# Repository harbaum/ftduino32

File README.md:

# ftDuino32

The ftDuino32 is the big brother of the [ftDuino](http://ftDuino.de). Read [more about the ftDuino32](https://harbaum.github.io/ftduino32/www/).

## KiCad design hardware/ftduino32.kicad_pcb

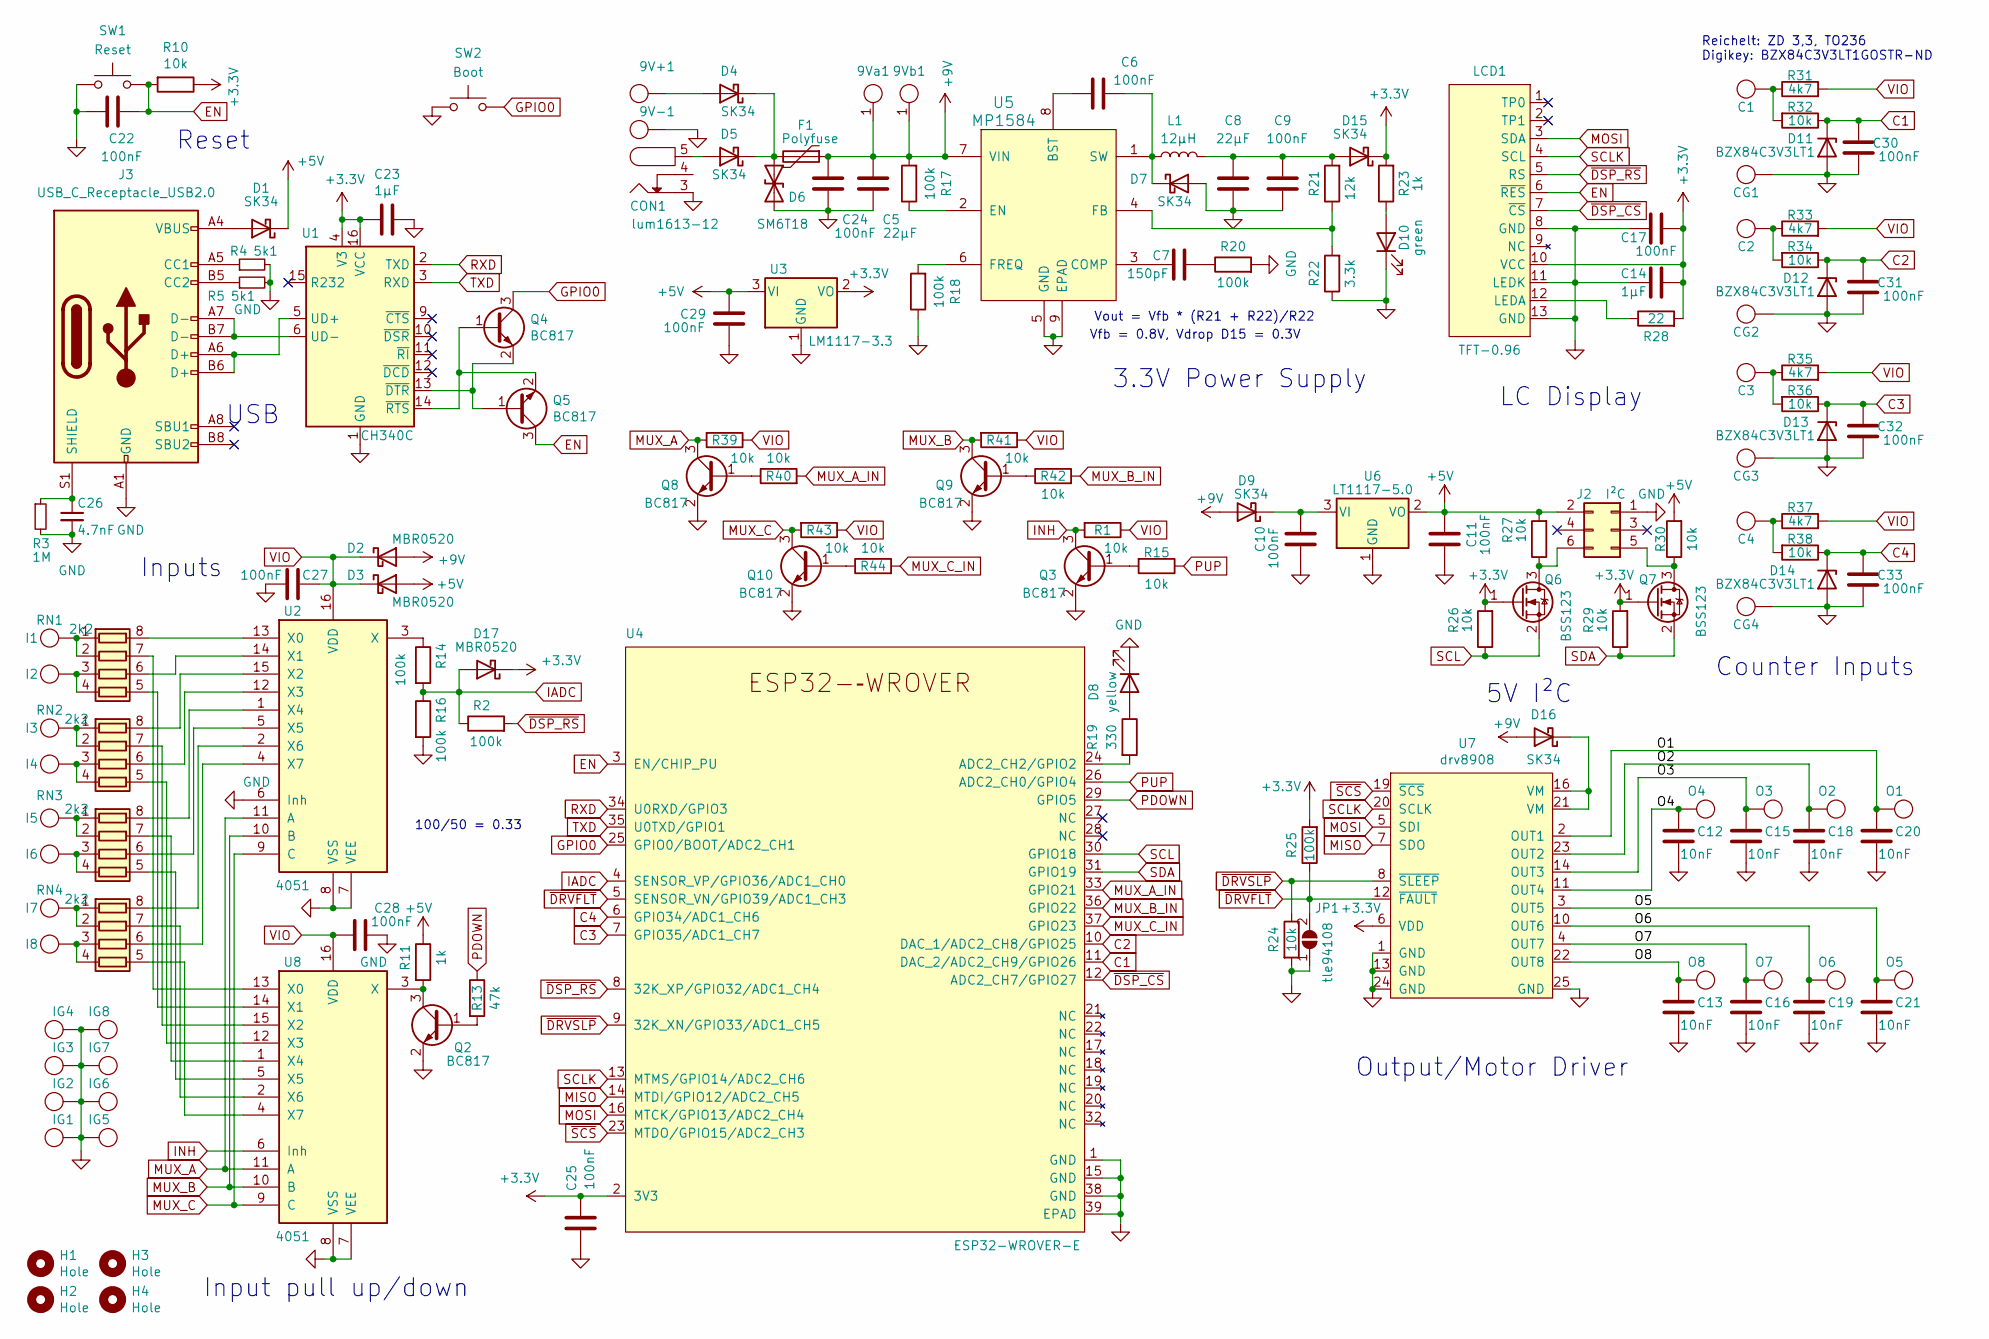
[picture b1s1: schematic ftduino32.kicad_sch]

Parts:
9V+1, 9V-1, 9Va1, 9Vb1: Sleeve; sleeve
C1, C2, C3, C4: Sleeve; sleeve
C5, C8: 22µF; C_1206_3216Metric; LCSC C12891
C6, C9, C10, C11, C17, C22, C24, C25, C27, C28, C29, C30, C31, C32, C33: 100nF; C_0805_2012Metric
C7: 150pF; C_0805_2012Metric
C12, C13, C15, C16, C18, C19, C20, C21: 10nF; C_0805_2012Metric
C14, C23: 1µF; C_0805_2012Metric
C26: 4.7nF; C_0805_2012Metric
CG1, CG2, CG3, CG4: Sleeve; sleeve
CON1: lum1613-12
D1, D4, D5, D7, D9, D15, D16: SK34; D_SMA; LCSC C8678
D2, D3, D17: MBR0520; D_SOD-123
D6: SM6T18; D_SMB
D8: yellow; LED_0805_2012Metric; LCSC C2296
D10: green; LED_0805_2012Metric; LCSC C2297
D11, D12, D13, D14: BZX84C3V3LT1; D_SOT-23_ANK; JLCPCB Rotation Offset 180
F1: Polyfuse; Fuse_1812_4532Metric; LCSC C207074
H1, H2, H3, H4: Hole; MountingHole_3mm
I1, I2, I3, I4, I5, I6, I7, I8: Sleeve; sleeve
IG1, IG2, IG3, IG4, IG5, IG6, IG7, IG8: Sleeve; sleeve
J2: I²C; PinHeader_2x03_P2.54mm_Vertical
J3: USB_C_Receptacle_USB2.0; TYPE-C-31-M-12; LCSC Part # C2927037
JP1: tle94108; SolderJumper-2_P1.3mm_Open_RoundedPad1.0x1.5mm
L1: 12µH; L_Abracon_ASPI-0630LR; LCSC C380177
LCD1: TFT-0.96
O1, O2, O3, O4, O5, O6, O7, O8: Sleeve; sleeve
Q2, Q3, Q4, Q5, Q8, Q9, Q10: BC817; SOT-23; JLCPCB Rotation Offset 180
Q6, Q7: BSS123; SOT-23; JLCPCB Rotation Offset 180
R1, R10, R15, R24, R26, R27, R29, R30, R32, R34, R36, R38, R39, R40, R41, R42, R43, R44: 10k; R_0805_2012Metric
R2, R14, R16, R17, R18, R20, R25: 100k; R_0805_2012Metric
R3: 1M; R_0805_2012Metric
R4, R5: 5k1; R_0805_2012Metric
R11, R23: 1k; R_0805_2012Metric
R13: 47k; R_0805_2012Metric
R19: 330; R_0805_2012Metric
R21: 12k; R_0805_2012Metric
R22: 3.3k; R_0805_2012Metric
R28: 22; R_0805_2012Metric
R31, R33, R35, R37: 4k7; R_0805_2012Metric
RN1, RN2, RN3, RN4: 2k2; R_Array_Convex_4x0603; JLCPCB Rotation Offset 90
SW1: Reset; SW_SPST_PTS645; LCSC C2837533
SW2: Boot; SW_SPST_PTS645; LCSC C2837533
U1: CH340C; SOIC-16_3.9x9.9mm_P1.27mm; JLCPCB Rotation Offset -90
U2, U8: 4051; TSSOP-16_4.4x5mm_P0.65mm; JLCPCB Rotation Offset -90
U3: LM1117-3.3; SOT-223-3_TabPin2; LCSC C6186
U4: ESP32-WROVER-E; JLCPCB Position Offset 0,-3.175
U5: MP1584; SOIC-8-1EP_3.9x4.9mm_P1.27mm_EP2.514x3.2mm_ThermalVias; JLCPCB Rotation Offset -90
U6: LT1117-5.0; SOT-223-3_TabPin2; JLCPCB Rotation Offset 180
U7: drv8908; HTSSOP-24-1EP_4.4x7.8mm_P0.65mm_EP3.4x7.8mm_Mask2.4x4.68mm_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

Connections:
+3V3: C14.1, C17.1, C23.2, C25.2, D15.1 (K), D17.1 (K), LCD1.10 (VCC), Q6.1 (G), Q7.1 (G), R10.1, R23.2, R25.2, R26.2, R28.2, R29.2, U1.4 (V3), U1.16 (VCC), U3.2 (VO), U4.2 (3V3), U7.6 (VDD)
+5V: C11.2, C29.2, D1.1 (K), D3.2 (A), J2.2, R11.1, R27.2, R30.2, U3.3 (VI), U6.2 (VO)
+9V: 9Va1.1, 9Vb1.1, C5.2, C24.2, D2.2 (A), D9.2 (A), D16.2 (A), F1.1, R17.2, U5.7 (VIN)
/O1: C20.2, O1.1, U7.2 (OUT1)
/O2: C18.2, O2.1, U7.23 (OUT2)
/O3: C15.2, O3.1, U7.14 (OUT3)
/O4: C12.2, O4.1, U7.11 (OUT4)
/O5: C21.2, O5.1, U7.3 (OUT5)
/O6: C19.2, O6.1, U7.10 (OUT6)
/O7: C16.2, O7.1, U7.4 (OUT7)
/O8: C13.2, O8.1, U7.22 (OUT8)
C1: C30.2, D11.1 (K), R32.1, U4.11 (DAC_2/ADC2_CH9/GPIO26)
C2: C31.2, D12.1 (K), R34.1, U4.10 (DAC_1/ADC2_CH8/GPIO25)
C3: C32.2, D13.1 (K), R36.1, U4.7 (GPIO35/ADC1_CH7)
C4: C33.2, D14.1 (K), R38.1, U4.6 (GPIO34/ADC1_CH6)
EN: C22.1, LCD1.6 (~RES), Q5.3 (C), R10.2, SW1.2, U4.3 (EN/CHIP_PU)
GND: 9V-1.1, C5.1, C8.1, C9.1, C10.1, C11.1, C12.1, C13.1, C14.2, C15.1, C16.1, C17.2, C18.1, C19.1, C20.1, C21.1, C22.2, C23.1, C24.1, C25.1, C26.2, C27.2, C28.1, C29.1, C30.1, C31.1, C32.1, C33.1, CG1.1, CG2.1, CG3.1, CG4.1, CON1.3, D6.2 (A2), D7.2 (A), D8.1 (K), D10.1 (K), D11.2 (A), D12.2 (A), D13.2 (A), D14.2 (A), IG1.1, IG2.1, IG3.1, IG4.1, IG5.1, IG6.1, IG7.1, IG8.1, J2.1, J3.A1 (GND), J3.A12 (GND), J3.B1 (GND), J3.B12 (GND), JP1.1 (A), LCD1.8 (GND), LCD1.11 (LEDK), LCD1.13 (GND), Q2.2 (E), Q3.2 (E), Q8.2 (E), Q9.2 (E), Q10.2 (E), R3.2, R4.2, R5.2, R16.2, R18.1, R20.2, R22.1, R24.2, SW1.1, SW2.1, U1.1 (GND), U2.6 (Inh), U2.7 (VEE), U2.8 (VSS), U3.1 (GND), U4.1 (GND), U4.15 (GND), U4.38 (GND), U4.39 (EPAD), U5.5 (GND), U5.9 (EPAD), U6.1 (GND), U7.1 (GND), U7.13 (GND), U7.24 (GND), U7.25 (GND), U8.7 (VEE), U8.8 (VSS)
GPIO0: Q4.3 (C), SW2.2, U4.25 (GPIO0/BOOT/ADC2_CH1)
IADC: D17.2 (A), R2.1, R14.2, R16.1, U4.4 (SENSOR_VP/GPIO36/ADC1_CH0)
INH: Q3.3 (C), R1.2, U8.6 (Inh)
MISO: U4.14 (MTDI/GPIO12/ADC2_CH5), U7.7 (SDO)
MOSI: LCD1.3 (SDA), U4.16 (MTCK/GPIO13/ADC2_CH4), U7.5 (SDI)
MUX_A: Q8.3 (C), R39.2, U2.11 (A), U8.11 (A)
MUX_A_IN: R40.2, U4.33 (GPIO21)
MUX_B: Q9.3 (C), R41.2, U2.10 (B), U8.10 (B)
MUX_B_IN: R42.2, U4.36 (GPIO22)
MUX_C: Q10.3 (C), R43.2, U2.9 (C), U8.9 (C)
MUX_C_IN: R44.2, U4.37 (GPIO23)
unnamed: C1.1, R31.1, R32.2
unnamed: C2.1, R33.1, R34.2
unnamed: C3.1, R35.1, R36.2
unnamed: C4.1, R37.1, R38.2
unnamed: C7.2, R20.1
unnamed: D1.2 (A), J3.A4 (VBUS), J3.A9 (VBUS), J3.B4 (VBUS), J3.B9 (VBUS)
unnamed: 9V+1.1, D4.2 (A)
unnamed: D4.1 (K), D5.1 (K), D6.1 (A1), F1.2
unnamed: CON1.5, D5.2 (A)
unnamed: C6.2, D7.1 (K), L1.1, U5.1 (SW)
unnamed: D8.2 (A), R19.1
unnamed: C10.2, D9.1 (K), U6.3 (VI)
unnamed: D10.2 (A), R23.1
unnamed: C8.2, C9.2, D15.2 (A), L1.2, R21.2
unnamed: D16.1 (K), U7.16 (VM), U7.21 (VM)
unnamed: J2.5, Q7.3 (D), R30.1
unnamed: J2.6, Q6.3 (D), R27.1
unnamed: J3.A5 (CC1), R4.1
unnamed: J3.B5 (CC2), R5.1
unnamed: C26.1, J3.S1 (SHIELD), R3.1
unnamed: LCD1.12 (LEDA), R28.1
unnamed: Q2.1 (B), R13.2
unnamed: Q2.3 (C), R11.2, U8.3 (X)
unnamed: Q3.1 (B), R15.2
unnamed: Q4.1 (B), Q5.2 (E), U1.14 (~RTS)
unnamed: Q4.2 (E), Q5.1 (B), U1.13 (~DTR)
unnamed: Q8.1 (B), R40.1
unnamed: Q9.1 (B), R42.1
unnamed: Q10.1 (B), R44.1
unnamed: I1.1, RN1.1 (R1.1), RN1.2 (R2.1)
unnamed: RN1.8 (R1.2), U2.13 (X0)
unnamed: RN1.7 (R2.2), U8.13 (X0)
unnamed: I2.1, RN1.3 (R3.1), RN1.4 (R4.1)
unnamed: RN1.6 (R3.2), U2.14 (X1)
unnamed: RN1.5 (R4.2), U8.14 (X1)
unnamed: I3.1, RN2.1 (R1.1), RN2.2 (R2.1)
unnamed: RN2.8 (R1.2), U2.15 (X2)
unnamed: RN2.7 (R2.2), U8.15 (X2)
unnamed: I4.1, RN2.3 (R3.1), RN2.4 (R4.1)
unnamed: RN2.6 (R3.2), U2.12 (X3)
unnamed: RN2.5 (R4.2), U8.12 (X3)
unnamed: I5.1, RN3.1 (R1.1), RN3.2 (R2.1)
unnamed: RN3.8 (R1.2), U2.1 (X4)
unnamed: RN3.7 (R2.2), U8.1 (X4)
unnamed: I6.1, RN3.3 (R3.1), RN3.4 (R4.1)
unnamed: RN3.6 (R3.2), U2.5 (X5)
unnamed: RN3.5 (R4.2), U8.5 (X5)
unnamed: I7.1, RN4.1 (R1.1), RN4.2 (R2.1)
unnamed: RN4.8 (R1.2), U2.2 (X6)
unnamed: RN4.7 (R2.2), U8.2 (X6)
unnamed: I8.1, RN4.3 (R3.1), RN4.4 (R4.1)
unnamed: RN4.6 (R3.2), U2.4 (X7)
unnamed: RN4.5 (R4.2), U8.4 (X7)
unnamed: J3.A6 (D+), J3.B6 (D+), U1.5 (UD+)
unnamed: J3.A7 (D-), J3.B7 (D-), U1.6 (UD-)
unnamed: R14.1, U2.3 (X)
unnamed: R19.2, U4.24 (ADC2_CH2/GPIO2)
unnamed: C6.1, U5.8 (BST)
unnamed: C7.1, U5.3 (COMP)
unnamed: R17.1, U5.2 (EN)
unnamed: R21.1, R22.2, U5.4 (FB)
unnamed: R18.2, U5.6 (FREQ)
PDOWN: R13.1, U4.29 (GPIO5)
PUP: R15.1, U4.26 (ADC2_CH0/GPIO4)
RXD: U1.2 (TXD), U4.34 (U0RXD/GPIO3)
SCL: Q6.2 (S), R26.1, U4.30 (GPIO18)
SCLK: LCD1.4 (SCL), U4.13 (MTMS/GPIO14/ADC2_CH6), U7.20 (SCLK)
SDA: Q7.2 (S), R29.1, U4.31 (GPIO19)
TXD: U1.3 (RXD), U4.35 (U0TXD/GPIO1)
VIO: C27.1, C28.2, D2.1 (K), D3.1 (K), R1.1, R31.2, R33.2, R35.2, R37.2, R39.1, R41.1, R43.1, U2.16 (VDD), U8.16 (VDD)
~DRVFLT: JP1.2 (B), R25.1, U4.5 (SENSOR_VN/GPIO39/ADC1_CH3), U7.12 (~FAULT)
~DRVSLP: R24.1, U4.9 (32K_XN/GPIO33/ADC1_CH5), U7.8 (~SLEEP)
~DSP_CS: LCD1.7 (~CS), U4.12 (ADC2_CH7/GPIO27)
~DSP_RS: LCD1.5 (RS), R2.2, U4.8 (32K_XP/GPIO32/ADC1_CH4)
~SCS: U4.23 (MTDO/GPIO15/ADC2_CH3), U7.19 (~SCS)

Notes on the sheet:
5V I²C
Input pull up/down
Reset
Output/Motor Driver
Vout = Vfb * (R21 + R22)/R22
3.3V Power Supply
Counter Inputs
Inputs
100/50 = 0.33
USB
LC Display
Vfb = 0.8V, Vdrop D15 = 0.3V
Reichelt: ZD 3,3, TO236 Digikey: BZX84C3V3LT1GOSTR-ND

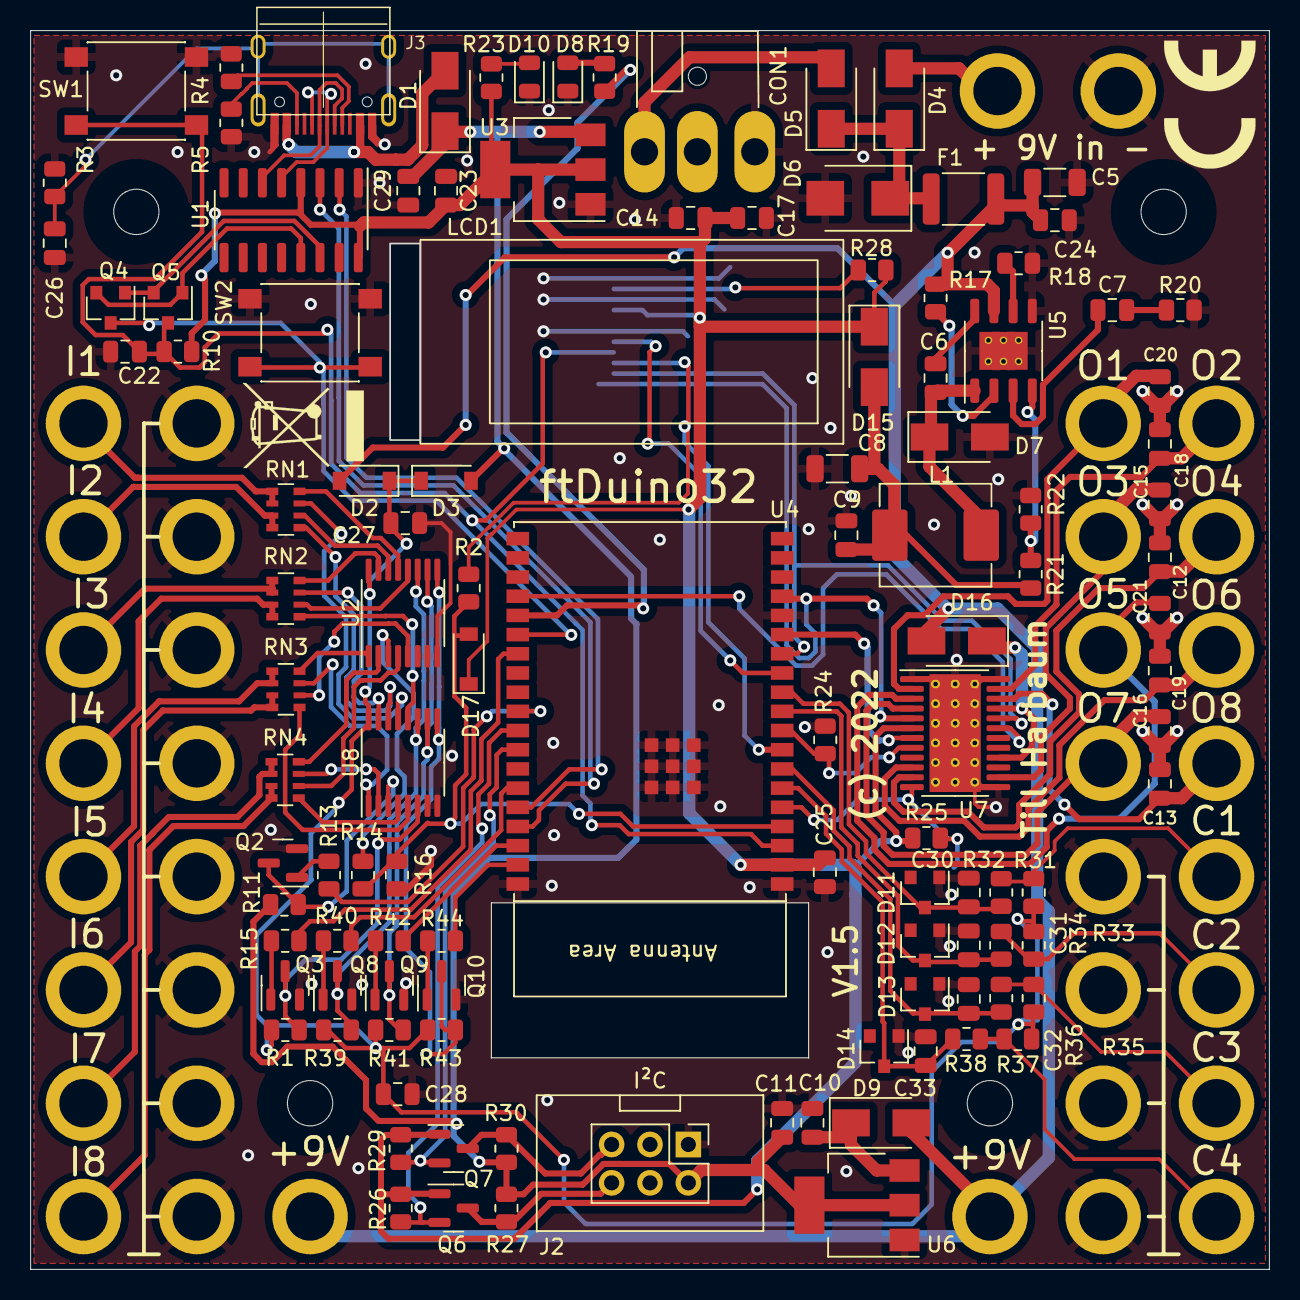
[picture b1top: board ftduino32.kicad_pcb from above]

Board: 2 copper layers, 82.0 x 82.0 mm, 155 parts (1 on the bottom side), 103 nets.

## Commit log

2023-04-24 Add web page stub
2023-04-24 Add photo
2023-04-24 Fix html
2023-04-28 Update web page
2023-04-29 Web cleanup
2023-04-29 Clean up image
2023-04-30 IDE comparison
2023-04-30 Fix typo
2023-04-30 Fix grid
2023-05-02 Wifi setup
2023-05-02 Update layout
2023-05-03 Wifi test
2023-05-03 Adjust image scaling
2023-05-04 ftDuino32 Micropython 1.20.0
2023-05-04 Add mac address patch
2023-05-04 Add mp readme
2023-05-04 Full image
2023-05-04 Link to upide
2023-05-04 Use screenshots instead of photos
2023-12-07 Add hardware

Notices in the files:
hardware/ftduino32.kicad_pcb:
(c) 2022
